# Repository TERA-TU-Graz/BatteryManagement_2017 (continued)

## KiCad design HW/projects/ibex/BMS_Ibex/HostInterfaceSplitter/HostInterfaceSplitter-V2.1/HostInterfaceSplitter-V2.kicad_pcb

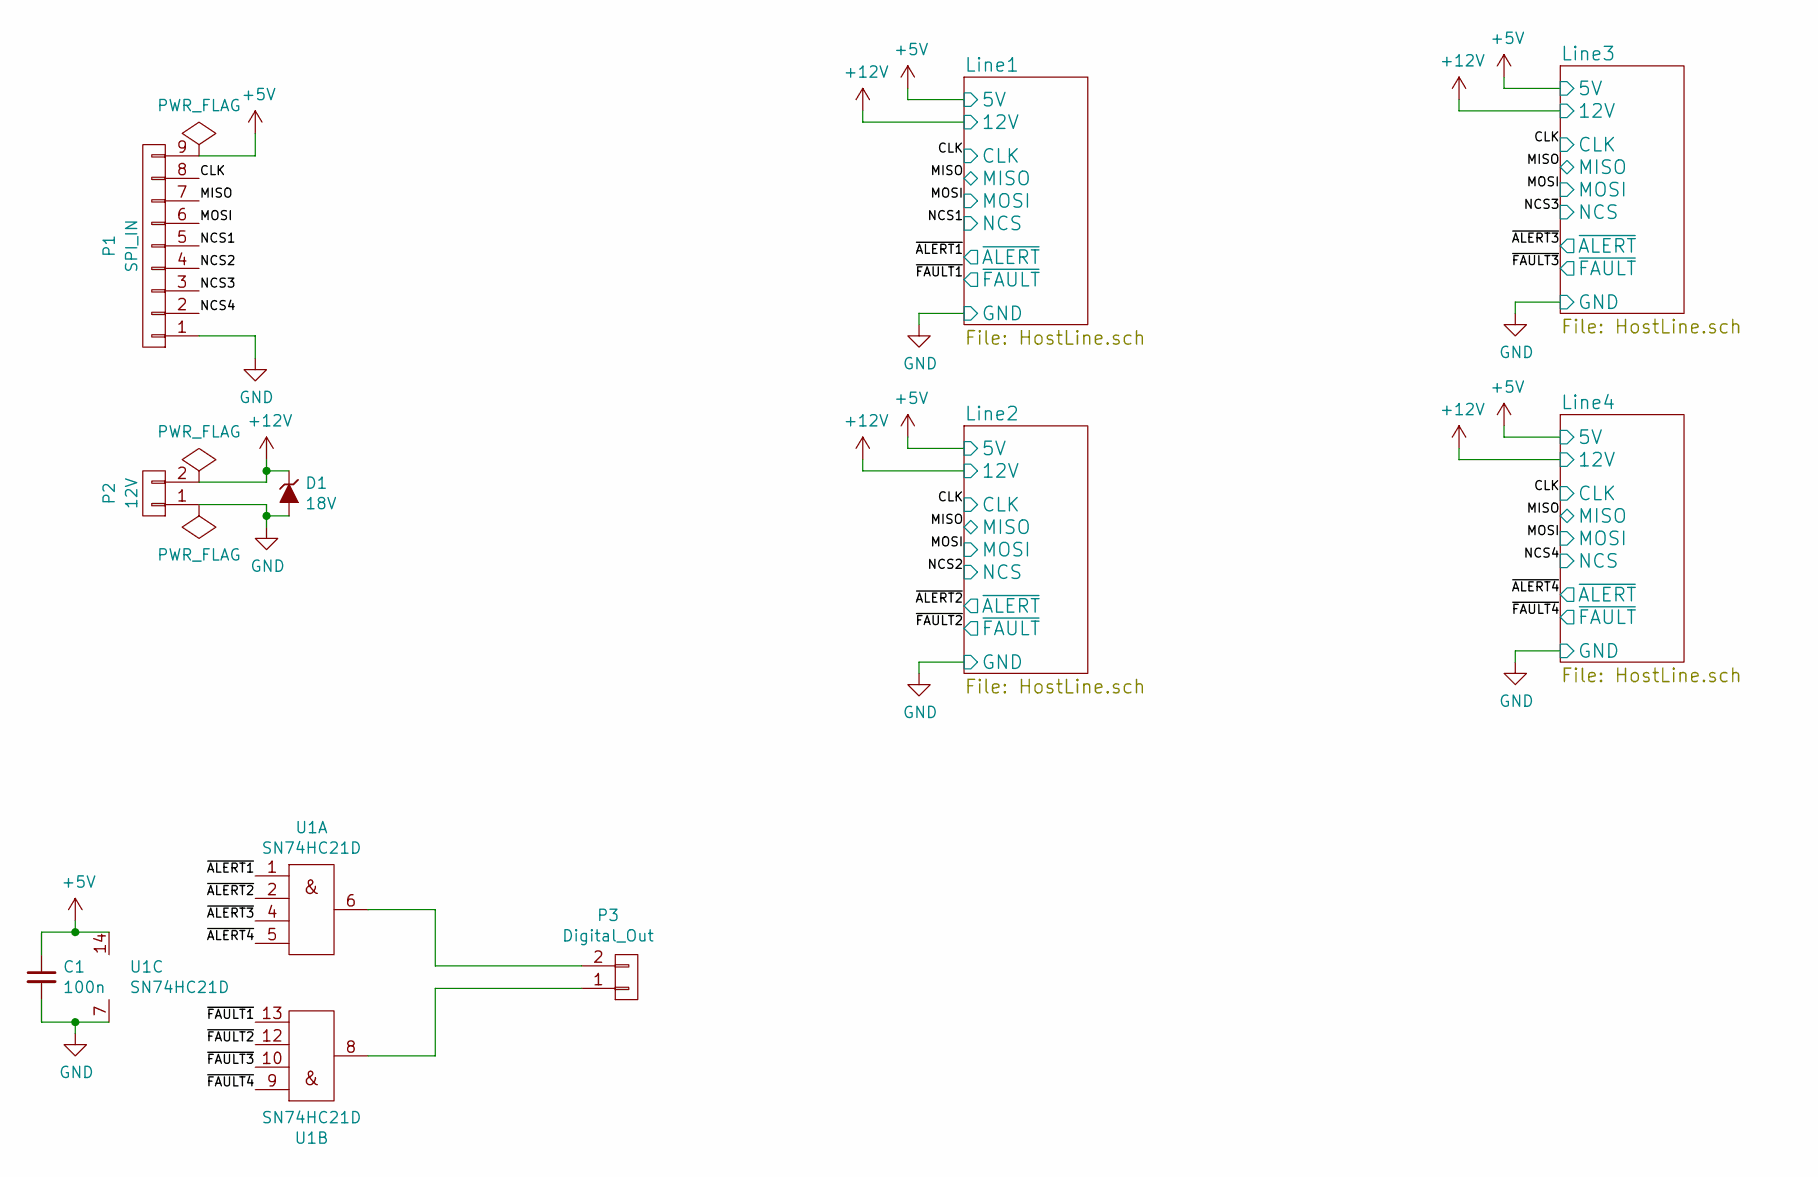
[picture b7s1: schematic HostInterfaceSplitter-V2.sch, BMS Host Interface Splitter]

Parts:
C1: 100n; C_0603in
D1: 18V; DO-214AA_with_vias_in_pad
P1: SPI_IN; JST_XH_B09B-XH-A_09x2.50mm_Straight
P2: 12V; JST_XH_B02B-XH-A_02x2.50mm_Straight
P3: Digital_Out; JST_EH_B02B-EH-A_02x2.50mm_Straight
U1: SN74HC21D

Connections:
+5V: C1.1, P1.9, U1.14 (VCC); also elsewhere on the board
+12V: D1.1 (K), P2.2; also elsewhere on the board
/CLK: P1.8; also elsewhere on the board
/MISO: P1.7; also elsewhere on the board
/MOSI: P1.6; also elsewhere on the board
/NCS1: P1.5; also elsewhere on the board
/NCS2: P1.4; also elsewhere on the board
/NCS3: P1.3; also elsewhere on the board
/NCS4: P1.2; also elsewhere on the board
/~ALERT1: U1.1 (1A); also elsewhere on the board
/~ALERT2: U1.2 (1B); also elsewhere on the board
/~ALERT3: U1.4 (1C); also elsewhere on the board
/~ALERT4: U1.5 (1D); also elsewhere on the board
/~FAULT1: U1.13 (2D); also elsewhere on the board
/~FAULT2: U1.12 (2C); also elsewhere on the board
/~FAULT3: U1.10 (2B); also elsewhere on the board
/~FAULT4: U1.9 (2A); also elsewhere on the board
GND: C1.2, D1.2 (A), P1.1, P2.1, U1.7 (GND); also elsewhere on the board
unnamed: P3.1, U1.8 (2Y)
unnamed: P3.2, U1.6 (1Y)

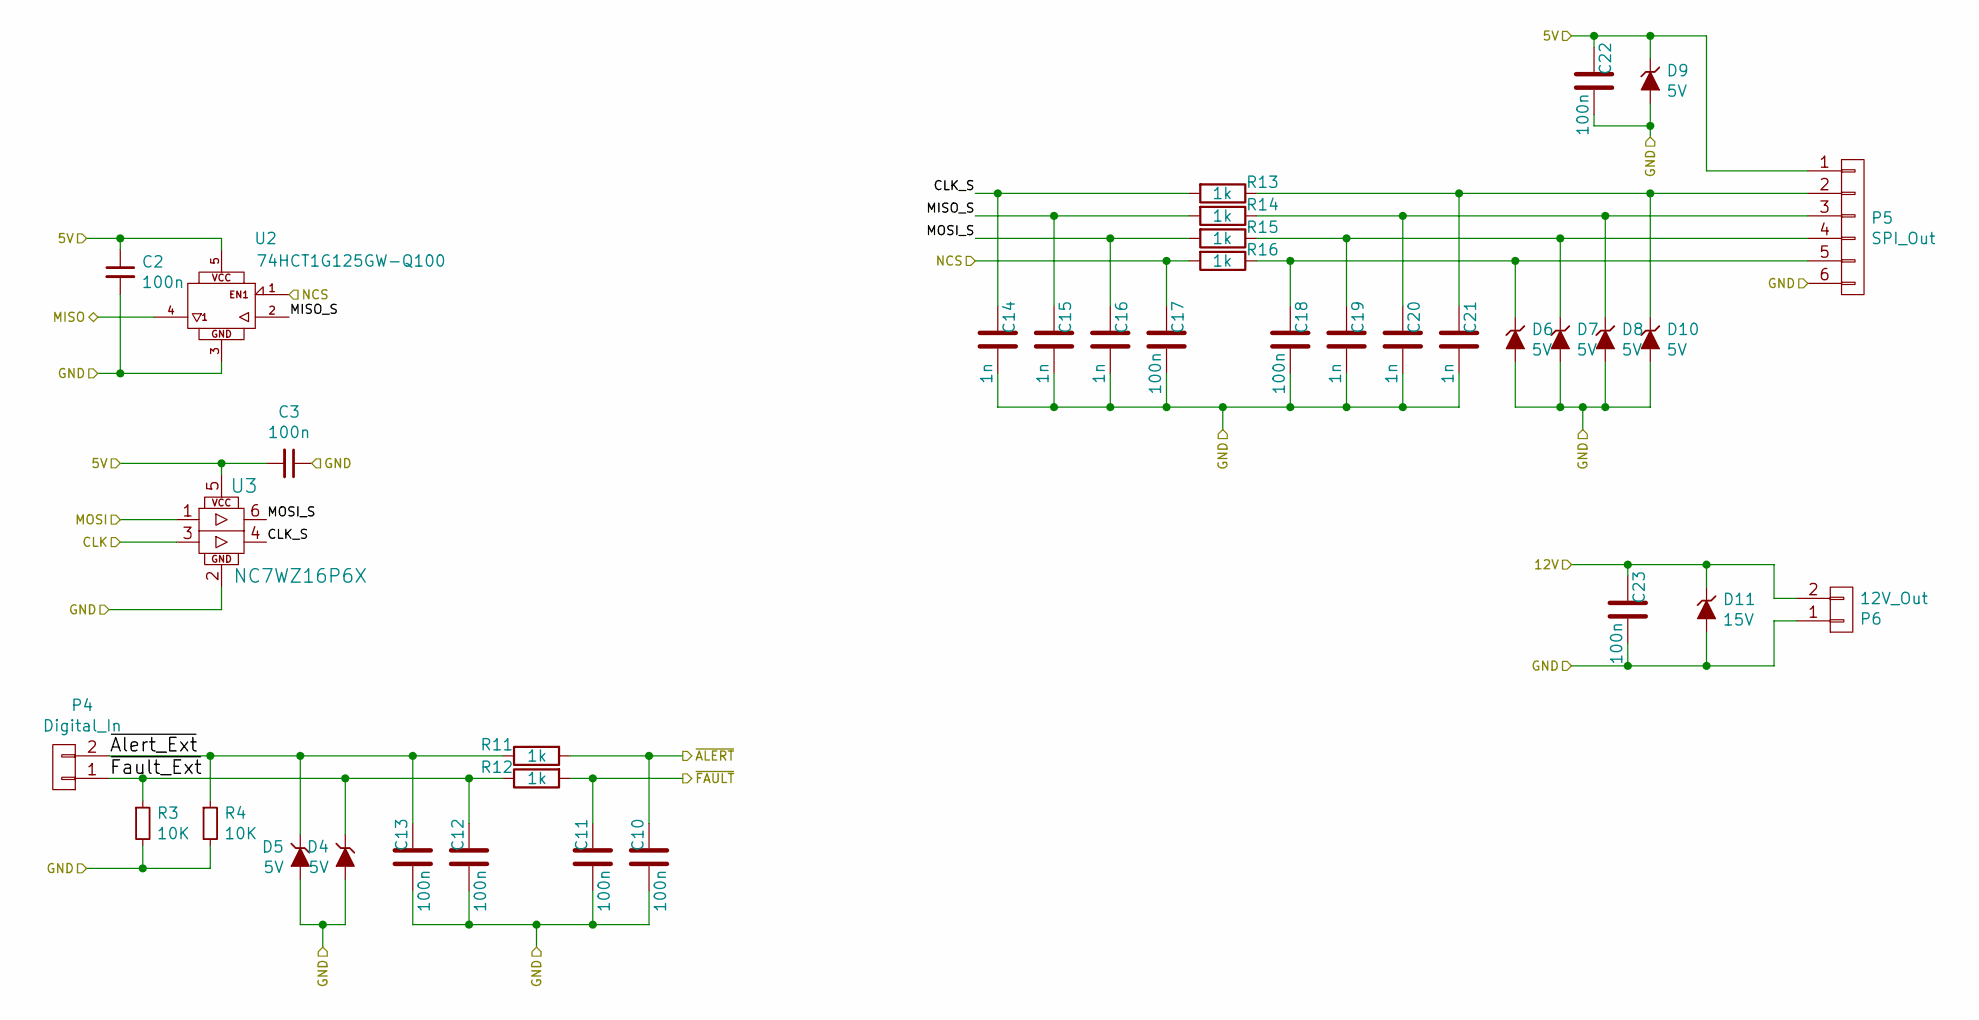
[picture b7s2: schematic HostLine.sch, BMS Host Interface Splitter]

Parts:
C2, C3, C10, C11, C12, C13, C17, C18, C22, C23: 100n; C_0603in
C14, C15, C16, C19, C20, C21: 1n; C_0603in
D4, D5, D6, D7, D8, D9, D10: 5V; SD05_tvs_5v
D11: 15V; CDSOD323-T15S_tvs_15v
P4: Digital_In; JST_EH_B02B-EH-A_02x2.50mm_Straight
P5: SPI_Out; Molex_PicoBlade_53398-0671_06x1.25mm_Straight
P6: 12V_Out; JST_XH_B02B-XH-A_02x2.50mm_Straight
R3, R4: 10K; R_0603in
R11, R12, R13, R14, R15, R16: 1k; R_0603in
U2: 74HCT1G125GW-Q100; 74HCT1G125GW-Q100H
U3: NC7WZ16P6X

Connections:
+5V: C2.1, C3.2, C22.2, D9.1 (K), P5.1, U2.5 (VCC), U3.5 (VCC); also elsewhere on the board
+12V: C23.2, D11.1 (K), P6.2; also elsewhere on the board
/CLK: U3.3 (A2); also elsewhere on the board
/Line1/CLK_S: C14.2, R13.2, U3.4 (Y2)
/Line1/MISO_S: C15.2, R14.2, U2.2 (A)
/Line1/MOSI_S: C16.2, R15.2, U3.6 (Y1)
/Line1/~Alert_Ext: C13.2, D5.1 (K), P4.2, R4.1, R11.1
/Line1/~Fault_Ext: C12.2, D4.1 (K), P4.1, R3.1, R12.1
/MISO: U2.4 (O); also elsewhere on the board
/MOSI: U3.1 (A1); also elsewhere on the board
/NCS1: C17.2, R16.2, U2.1 (EN); also elsewhere on the board
/~ALERT1: C10.2, R11.2; also elsewhere on the board
/~FAULT1: C11.2, R12.2; also elsewhere on the board
GND: C2.2, C3.1, C10.1, C11.1, C12.1, C13.1, C14.1, C15.1, C16.1, C17.1, C18.1, C19.1, C20.1, C21.1, C22.1, C23.1, D4.2 (A), D5.2 (A), D6.2 (A), D7.2 (A), D8.2 (A), D9.2 (A), D10.2 (A), D11.2 (A), P5.6, P6.1, R3.2, R4.2, U2.3 (GND), U3.2 (GND); also elsewhere on the board
unnamed: C18.2, D6.1 (K), P5.5, R16.1
unnamed: C19.2, D7.1 (K), P5.4, R15.1
unnamed: C20.2, D8.1 (K), P5.3, R14.1
unnamed: C21.2, D10.1 (K), P5.2, R13.1

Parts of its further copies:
C4, C5, C6, C7, C8, C9, C24, C25, C26, C27, C31, C32, C36, C37, C38, C39, C40, C41, C45, C46, C50, C51, C52, C53, C54, C55, C59, C60, C64, C65: 100n; C_0603in
C28, C29, C30, C33, C34, C35, C42, C43, C44, C47, C48, C49, C56, C57, C58, C61, C62, C63: 1n; C_0603in
D12, D13, D14, D15, D16, D17, D18, D20, D21, D22, D23, D24, D25, D26, D28, D29, D30, D31, D32, D33, D34: 5V; SD05_tvs_5v
D19, D27, D35: 15V; CDSOD323-T15S_tvs_15v
P7, P10, P13: Digital_In; JST_EH_B02B-EH-A_02x2.50mm_Straight
P8, P11, P14: SPI_Out; Molex_PicoBlade_53398-0671_06x1.25mm_Straight
P9, P12, P15: 12V_Out; JST_XH_B02B-XH-A_02x2.50mm_Straight
R5, R6, R7, R8, R9, R10: 10K; R_0603in
R17, R18, R19, R20, R21, R22, R23, R24, R25, R26, R27, R28, R29, R30, R31, R32, R33, R34: 1k; R_0603in
U4, U6, U8: 74HCT1G125GW-Q100; 74HCT1G125GW-Q100H
U5, U7, U9: NC7WZ16P6X

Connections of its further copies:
+5V: C4.1, C5.2, C6.1, C7.2, C8.1, C9.2, C36.2, C50.2, C64.2, D17.1 (K), D25.1 (K), D33.1 (K), P8.1, P11.1, P14.1, U4.5 (VCC), U5.5 (VCC), U6.5 (VCC), U7.5 (VCC), U8.5 (VCC), U9.5 (VCC); also elsewhere on the board
+12V: C37.2, C51.2, C65.2, D19.1 (K), D27.1 (K), D35.1 (K), P9.2, P12.2, P15.2; also elsewhere on the board
/CLK: U5.3 (A2), U7.3 (A2), U9.3 (A2); also elsewhere on the board
/Line2/CLK_S: C28.2, R19.2, U5.4 (Y2)
/Line2/MISO_S: C29.2, R20.2, U4.2 (A)
/Line2/MOSI_S: C30.2, R21.2, U5.6 (Y1)
/Line2/~Alert_Ext: C27.2, D13.1 (K), P7.2, R6.1, R17.1
/Line2/~Fault_Ext: C26.2, D12.1 (K), P7.1, R5.1, R18.1
/Line3/CLK_S: C42.2, R25.2, U7.4 (Y2)
/Line3/MISO_S: C43.2, R26.2, U6.2 (A)
/Line3/MOSI_S: C44.2, R27.2, U7.6 (Y1)
/Line3/~Alert_Ext: C41.2, D21.1 (K), P10.2, R8.1, R23.1
/Line3/~Fault_Ext: C40.2, D20.1 (K), P10.1, R7.1, R24.1
/Line4/CLK_S: C56.2, R31.2, U9.4 (Y2)
/Line4/MISO_S: C57.2, R32.2, U8.2 (A)
/Line4/MOSI_S: C58.2, R33.2, U9.6 (Y1)
/Line4/~Alert_Ext: C55.2, D29.1 (K), P13.2, R10.1, R29.1
/Line4/~Fault_Ext: C54.2, D28.1 (K), P13.1, R9.1, R30.1
/MISO: U4.4 (O), U6.4 (O), U8.4 (O); also elsewhere on the board
/MOSI: U5.1 (A1), U7.1 (A1), U9.1 (A1); also elsewhere on the board
/NCS2: C31.2, R22.2, U4.1 (EN); also elsewhere on the board
/NCS3: C45.2, R28.2, U6.1 (EN); also elsewhere on the board
/NCS4: C59.2, R34.2, U8.1 (EN); also elsewhere on the board
/~ALERT2: C24.2, R17.2; also elsewhere on the board
/~ALERT3: C38.2, R23.2; also elsewhere on the board
/~ALERT4: C52.2, R29.2; also elsewhere on the board
/~FAULT2: C25.2, R18.2; also elsewhere on the board
/~FAULT3: C39.2, R24.2; also elsewhere on the board
/~FAULT4: C53.2, R30.2; also elsewhere on the board
GND: C4.2, C5.1, C6.2, C7.1, C8.2, C9.1, C24.1, C25.1, C26.1, C27.1, C28.1, C29.1, C30.1, C31.1, C32.1, C33.1, C34.1, C35.1, C36.1, C37.1, C38.1, C39.1, C40.1, C41.1, C42.1, C43.1, C44.1, C45.1, C46.1, C47.1, C48.1, C49.1, C50.1, C51.1, C52.1, C53.1, C54.1, C55.1, C56.1, C57.1, C58.1, C59.1, C60.1, C61.1, C62.1, C63.1, C64.1, C65.1, D12.2 (A), D13.2 (A), D14.2 (A), D15.2 (A), D16.2 (A), D17.2 (A), D18.2 (A), D19.2 (A), D20.2 (A), D21.2 (A), D22.2 (A), D23.2 (A), D24.2 (A), D25.2 (A), D26.2 (A), D27.2 (A), D28.2 (A), D29.2 (A), D30.2 (A), D31.2 (A), D32.2 (A), D33.2 (A), D34.2 (A), D35.2 (A), P8.6, P9.1, P11.6, P12.1, P14.6, P15.1, R5.2, R6.2, R7.2, R8.2, R9.2, R10.2, U4.3 (GND), U5.2 (GND), U6.3 (GND), U7.2 (GND), U8.3 (GND), U9.2 (GND); also elsewhere on the board
unnamed: C32.2, D14.1 (K), P8.5, R22.1
unnamed: C33.2, D15.1 (K), P8.4, R21.1
unnamed: C34.2, D16.1 (K), P8.3, R20.1
unnamed: C35.2, D18.1 (K), P8.2, R19.1
unnamed: C46.2, D22.1 (K), P11.5, R28.1
unnamed: C47.2, D23.1 (K), P11.4, R27.1
unnamed: C48.2, D24.1 (K), P11.3, R26.1
unnamed: C49.2, D26.1 (K), P11.2, R25.1
unnamed: C60.2, D30.1 (K), P14.5, R34.1
unnamed: C61.2, D31.1 (K), P14.4, R33.1
unnamed: C62.2, D32.1 (K), P14.3, R32.1
unnamed: C63.2, D34.1 (K), P14.2, R31.1

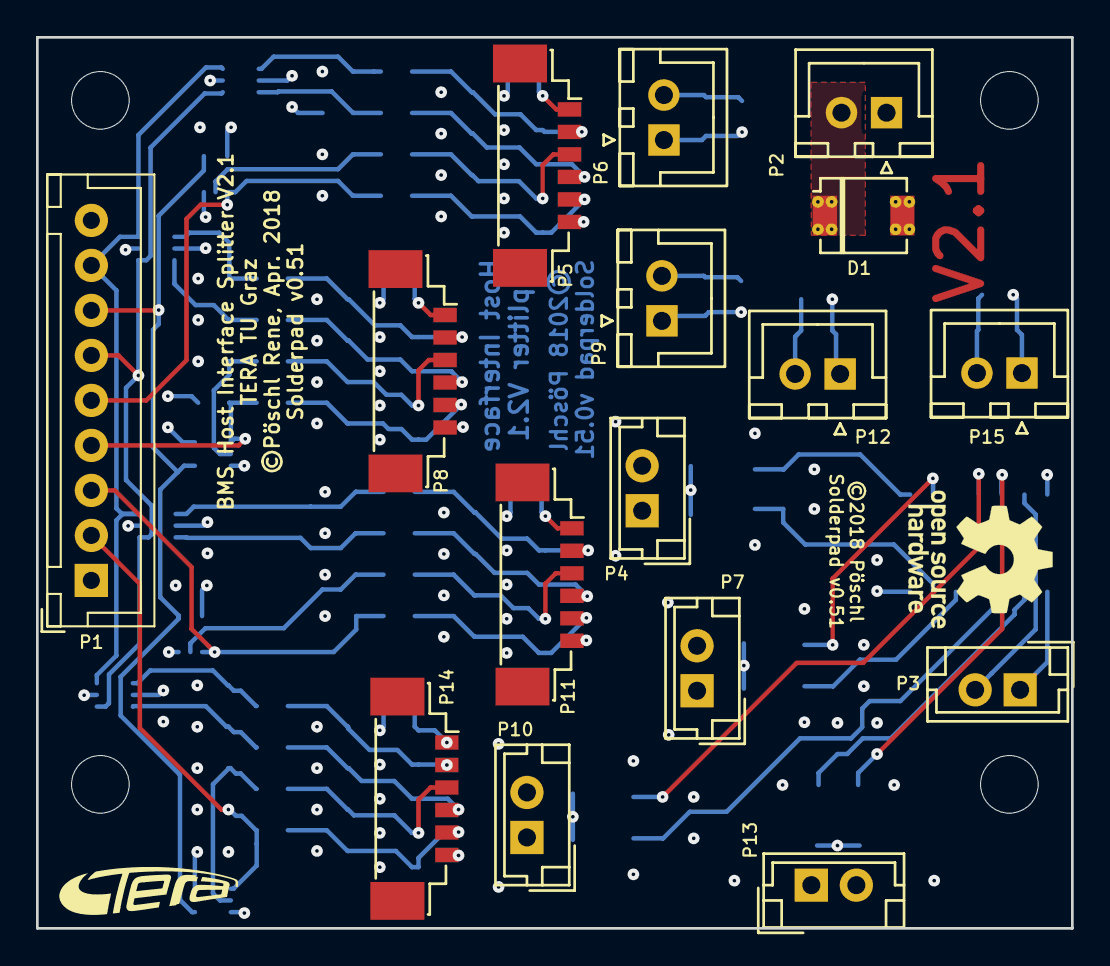
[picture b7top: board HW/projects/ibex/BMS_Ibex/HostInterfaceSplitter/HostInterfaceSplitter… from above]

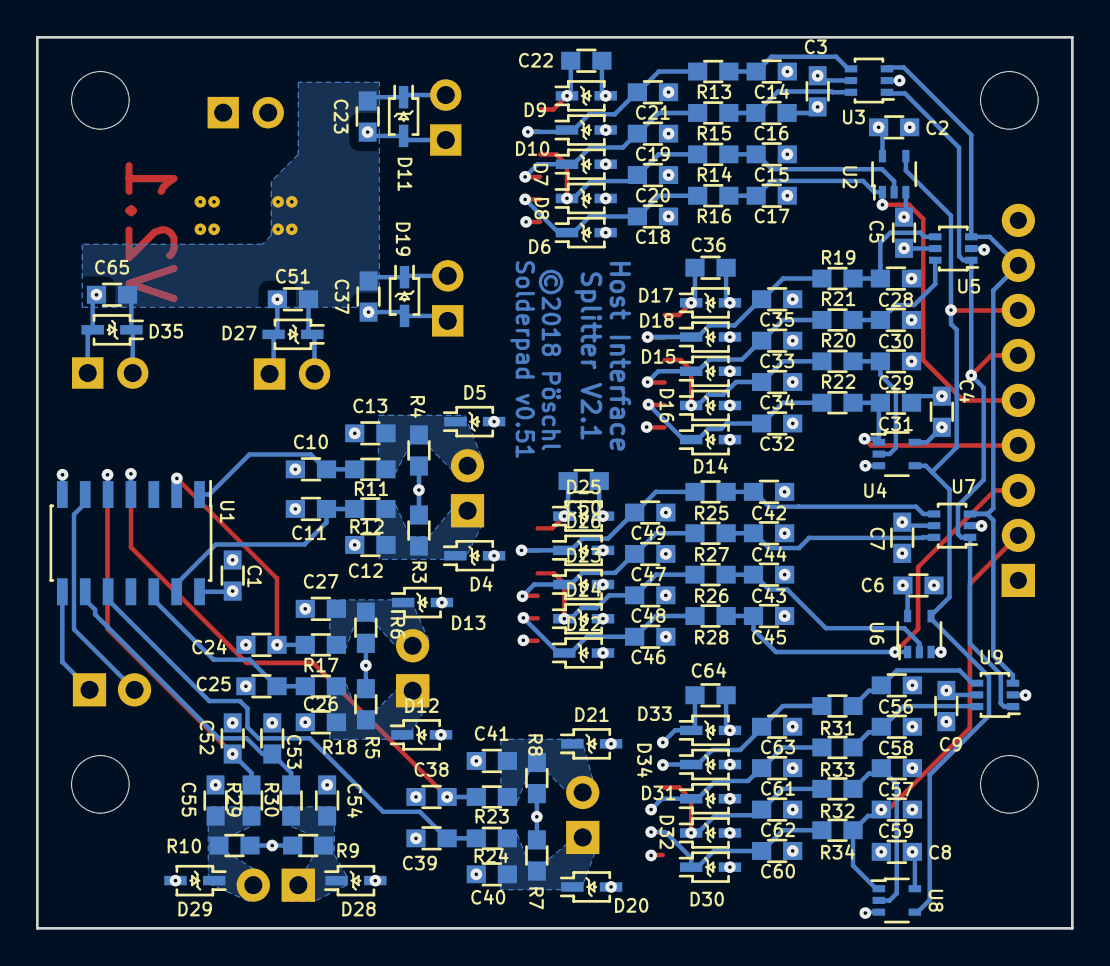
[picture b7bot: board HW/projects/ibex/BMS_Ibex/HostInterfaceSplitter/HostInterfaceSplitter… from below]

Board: 4 copper layers, 57.5 x 49.5 mm, 155 parts (138 on the bottom side), 56 nets.

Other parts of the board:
svg2mod: G***; TERA_TextOnly_SilkS_2.5x9.5mm

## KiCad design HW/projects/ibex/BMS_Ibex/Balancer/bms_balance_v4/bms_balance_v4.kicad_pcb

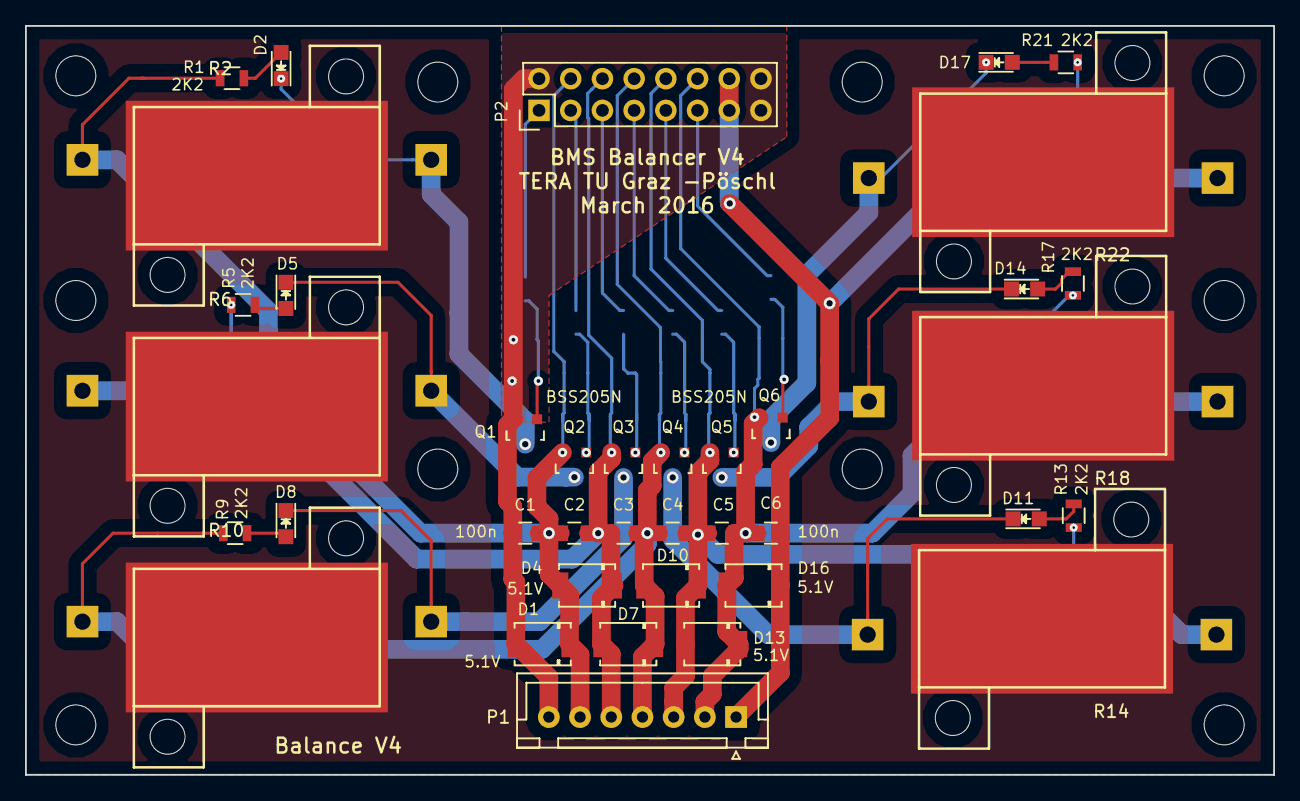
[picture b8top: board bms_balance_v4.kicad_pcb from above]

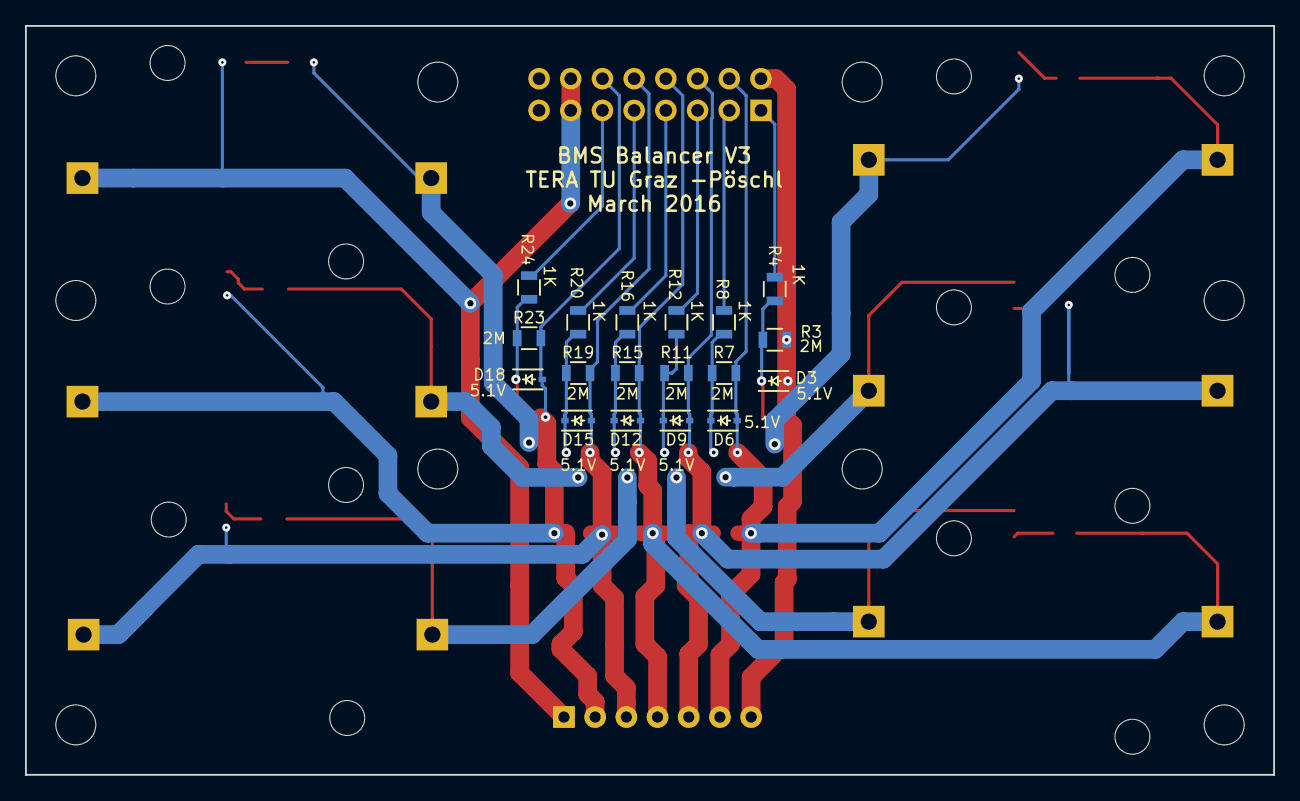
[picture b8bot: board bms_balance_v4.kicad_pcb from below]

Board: 2 copper layers, 100.0 x 60.0 mm, 56 parts (18 on the bottom side), 32 nets.

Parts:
C1, C2, C3, C4, C5, C6: 100n; C_0805
D1, D4, D7, D10, D13, D16: 5.1V; DO-214AA
D2, D5, D8, D11, D14, D17: LED; LED_0805
D3, D6, D9, D12, D15, D18: 5.1V; SOD-323
P1: CONN_01X07; JST_XH_B07B-XH-A_07x2.50mm_Straight
P2: CONN_02X08; Pin_Header_Straight_2x08
Q1, Q2, Q3, Q4, Q5, Q6: BSS205N; SOT-23
R1, R5, R9, R13, R17, R21: 2K2; R_0805
R2, R6, R10, R14, R18, R22: 3R3; HS15-1EP
R3, R7, R11, R15, R19, R23: 2M; R_0805
R4, R8, R12, R16, R20, R24: 1K; R_0805

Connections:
+BATT: C6.1, D16.1, P1.1, P2.13, P2.14, R21.1, R22.1
/BalancerCell1/Heat: R2.3, R6.3, R10.3, R14.3, R18.3, R22.3
/CB1: P2.1, R4.1
/CB2: P2.3, R8.1
/CB3: P2.5, R12.1
/CB4: P2.7, R16.1
/CB5: P2.9, R20.1
/CB6: P2.11, R24.1
/V1: C1.1, C2.2, D1.1, D4.2, D6.2, P1.6, P2.4, Q2.2, R1.1, R2.1, R7.2
/V2: C2.1, C3.2, D4.1, D7.2, D9.2, P1.5, P2.6, Q3.2, R5.1, R6.1, R11.2
/V3: C3.1, C4.2, D7.1, D10.2, D12.2, P1.4, P2.8, Q4.2, R9.1, R10.1, R15.2
/V4: C4.1, C5.2, D10.1, D13.2, D15.2, P1.3, P2.10, Q5.2, R13.1, R14.1, R19.2
/V5: C5.1, C6.2, D13.1, D16.2, D18.2, P1.2, P2.12, Q6.2, R17.1, R18.1, R23.2
GND: C1.2, D1.2, D3.2, P1.7, P2.2, P2.15, P2.16, Q1.2, R3.2
unnamed: D2.1, Q1.3, R2.2
unnamed: D2.2, R1.2
unnamed: D3.1, Q1.1, R3.1, R4.2
unnamed: D5.1, Q2.3, R6.2
unnamed: D5.2, R5.2
unnamed: D6.1, Q2.1, R7.1, R8.2
unnamed: D8.1, Q3.3, R10.2
unnamed: D8.2, R9.2
unnamed: D9.1, Q3.1, R11.1, R12.2
unnamed: D11.1, Q4.3, R14.2
unnamed: D11.2, R13.2
unnamed: D12.1, Q4.1, R15.1, R16.2
unnamed: D14.1, Q5.3, R18.2
unnamed: D14.2, R17.2
unnamed: D15.1, Q5.1, R19.1, R20.2
unnamed: D17.1, Q6.3, R22.2
unnamed: D17.2, R21.2
unnamed: D18.1, Q6.1, R23.1, R24.2

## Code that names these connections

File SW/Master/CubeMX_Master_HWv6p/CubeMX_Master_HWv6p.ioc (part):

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Mcu.Name=STM32F405RGTx
Mcu.Package=LQFP64
Mcu.UserName=STM32F405RGTx
PA1.GPIOParameters=GPIO_Label
PA1.GPIO_Label=LEM1
PA1.Signal=ADCx_IN1
PA10.GPIOParameters=GPIO_Label
PA10.GPIO_Label=CAN1_RS
PA10.Signal=GPIO_Output
PA11.Mode=Master
PA11.Signal=CAN1_RX
PA12.Mode=Master
PA12.Signal=CAN1_TX
PA13.Mode=JTAG_5_pins
PA13.Signal=SYS_JTMS-SWDIO
PA14.Mode=JTAG_5_pins
PA14.Signal=SYS_JTCK-SWCLK
PA15.Mode=JTAG_5_pins
PA15.Signal=SYS_JTDI
PA2.GPIOParameters=GPIO_Label
PA2.GPIO_Label=LEM2
PA2.Signal=ADCx_IN2
PA3.GPIOParameters=GPIO_Label
PA3.GPIO_Label=WHEEL_SPEED
PA3.Signal=S_TIM2_CH4
PA4.GPIOParameters=GPIO_Label,GPIO_ModeDefaultOutputPP
PA4.GPIO_Label=SPI1_CS_B0
PA4.GPIO_ModeDefaultOutputPP=GPIO_MODE_OUTPUT_OD
PA4.Signal=GPIO_Output
PA5.Mode=Full_Duplex_Master
PA5.Signal=SPI1_SCK
PA6.Mode=Full_Duplex_Master
PA6.Signal=SPI1_MISO
PA7.Mode=Full_Duplex_Master
PA7.Signal=SPI1_MOSI
PA8.GPIOParameters=GPIO_Label
PA8.GPIO_Label=SuperCharger_On
PA8.Signal=GPIO_Input
PA9.GPIOParameters=GPIO_Label
PA9.GPIO_Label=SuperCharger_Fault
PA9.Signal=GPIO_Input
PB0.GPIOParameters=GPIO_Speed,GPIO_Label,GPIO_ModeDefaultOutputPP
PB0.GPIO_Label=SPI1_CS
PB0.GPIO_ModeDefaultOutputPP=GPIO_MODE_OUTPUT_OD
PB0.GPIO_Speed=GPIO_SPEED_FREQ_HIGH
PB0.Signal=GPIO_Output
PB1.GPIOParameters=GPIO_Label
PB1.GPIO_Label=Main_on
PB1.Signal=GPIO_Input
PB10.GPIOParameters=GPIO_Label
PB10.GPIO_Label=N_Alert
PB10.Signal=GPIO_Input
PB11.GPIOParameters=GPIO_Label
PB11.GPIO_Label=FAN_Fault
PB11.Signal=GPIO_Input
PB12.Mode=Slave
PB12.Signal=CAN2_RX
PB13.Mode=Slave
PB13.Signal=CAN2_TX
PB14.GPIOParameters=GPIO_Label
PB14.GPIO_Label=CAN2_RS
PB14.Signal=GPIO_Output
PB15.GPIOParameters=GPIO_Label,GPIO_ModeDefaultOutputPP
PB15.GPIO_Label=SPI1_CS_B1
PB15.GPIO_ModeDefaultOutputPP=GPIO_MODE_OUTPUT_OD
PB15.Signal=GPIO_Output
PB2.GPIOParameters=GPIO_Label
PB2.GPIO_Label=Main_fault
PB2.Signal=GPIO_Input
PB3.Mode=JTAG_5_pins
PB3.Signal=SYS_JTDO-SWO
PB4.Mode=JTAG_5_pins
PB4.Signal=SYS_JTRST
PB5.GPIOParameters=GPIO_Label
PB5.GPIO_Label=LED1
PB5.Signal=GPIO_Output
PB6.GPIOParameters=GPIO_Label
PB6.GPIO_Label=Interlock_On1
PB6.Signal=GPIO_Output
PB7.GPIOParameters=GPIO_Label
PB7.GPIO_Label=Interlock_On2
PB7.Signal=GPIO_Output
PC0.GPIOParameters=GPIO_Label
PC0.GPIO_Label=TS1
PC0.Signal=ADCx_IN10
PC1.GPIOParameters=GPIO_Label
PC1.GPIO_Label=TS2
PC1.Signal=ADCx_IN11
PC10.Mode=Asynchronous
PC10.Signal=UART4_TX
PC11.Mode=Asynchronous
PC11.Signal=UART4_RX
PC12.GPIOParameters=GPIO_Label
PC12.GPIO_Label=LED3
PC12.Signal=GPIO_Output
PC13-ANTI_TAMP.GPIOParameters=GPIO_PuPd,GPIO_Label
PC13-ANTI_TAMP.GPIO_Label=BUTTON_ON
PC13-ANTI_TAMP.GPIO_PuPd=GPIO_PULLDOWN
PC13-ANTI_TAMP.Signal=GPIO_Input
PC14-OSC32_IN.GPIOParameters=GPIO_PuPd,GPIO_Label
PC14-OSC32_IN.GPIO_Label=BUTTON_OFF
PC14-OSC32_IN.GPIO_PuPd=GPIO_PULLDOWN
PC14-OSC32_IN.Signal=GPIO_Input
PC2.GPIOParameters=GPIO_Label
PC2.GPIO_Label=TS3
PC2.Signal=ADCx_IN12
PC3.GPIOParameters=GPIO_Label
PC3.GPIO_Label=TS4
PC3.Signal=ADCx_IN13
PC4.GPIOParameters=GPIO_PuPd,GPIO_Label
PC4.GPIO_Label=Interlock_OK
PC4.GPIO_PuPd=GPIO_PULLDOWN
PC4.Signal=GPIO_Input
PC5.GPIOParameters=GPIO_Label
PC5.GPIO_Label=N_TMP_REF_SHDN
PC5.Signal=GPIO_Output
PC6.GPIOParameters=GPIO_Label,GPIO_ModeDefaultOutputPP
PC6.GPIO_Label=SPI1_CS_B2
PC6.GPIO_ModeDefaultOutputPP=GPIO_MODE_OUTPUT_OD
PC6.Signal=GPIO_Output
PC7.GPIOParameters=GPIO_Label
PC7.GPIO_Label=N_Fault
PC7.Signal=GPIO_Input
PC8.GPIOParameters=GPIO_Label
PC8.GPIO_Label=Precharge_fault
PC8.Signal=GPIO_Input
PC9.GPIOParameters=GPIO_Label
PC9.GPIO_Label=FAN_PWM
PC9.Signal=S_TIM3_CH4
PD2.GPIOParameters=GPIO_Label
PD2.GPIO_Label=LED2
PD2.Signal=GPIO_Output
PH0-OSC_IN.Mode=HSE-External-Oscillator
PH0-OSC_IN.Signal=RCC_OSC_IN
PH1-OSC_OUT.Mode=HSE-External-Oscillator
PH1-OSC_OUT.Signal=RCC_OSC_OUT
RCC.HSE_VALUE=8000000
RCC.SYSCLKFreq_VALUE=168000000
RCC.SYSCLKSource=RCC_SYSCLKSOURCE_PLLCLK
board=CubeMX_Master_HWv6p

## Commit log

2017-08-10 Initial commit software.
2017-08-10 Adding kicad libs
2017-08-10 Adding PCB files
2017-08-10 Adding license file
2018-10-28 Update github repo with designs for fennek 2018
2018-10-28 Update submodule for libraries
2018-10-28 update submodule container for general projects
2018-10-28 Sync ibex bms with tera local
